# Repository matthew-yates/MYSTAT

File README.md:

## MYSTAT Potentiostat/Galvanostat

These are the design files for building and operating a compact open source potentiostat/galvanostat instrument.  The detailed technical specifications and instructions for operation can be found in the HardwareX article [MYSTAT: A compact potentiostat/galvanostat for general electrochemistry measurements](https://www.hardware-x.com/article/S2468-0672(20)30072-9/fulltext). The HardwareX article has a link to a static repository at [Zenodo](https://zenodo.org/records/4252476).  This github repository was created as a clone of the Zenodo repository, with the goal of facilitating the tracking of improvements to hardware design and development of control software.

The MYSTAT instrument design and control software is based on an earlier open source design published by [Thomas Dobbelaere](https://www.hardware-x.com/article/S2468-0672(17)30031-7/fulltext), who also created a [github repository](https://github.com/thomasdob/tdstatv3) for that instrument.

The voltage and current ranges of MYSTAT are significantly higher than the original design of Dobbelaere. The printed circuit board was completely redesigned. Only relatively minor changes were made to the Python control software and microcontroller firmware originally created by Dobbelaere.

This hardware and control software is fully open source, and changes/improvements are welcome.  An entirely open source tool chain was used for its development (KiCad, Python, and Linux).

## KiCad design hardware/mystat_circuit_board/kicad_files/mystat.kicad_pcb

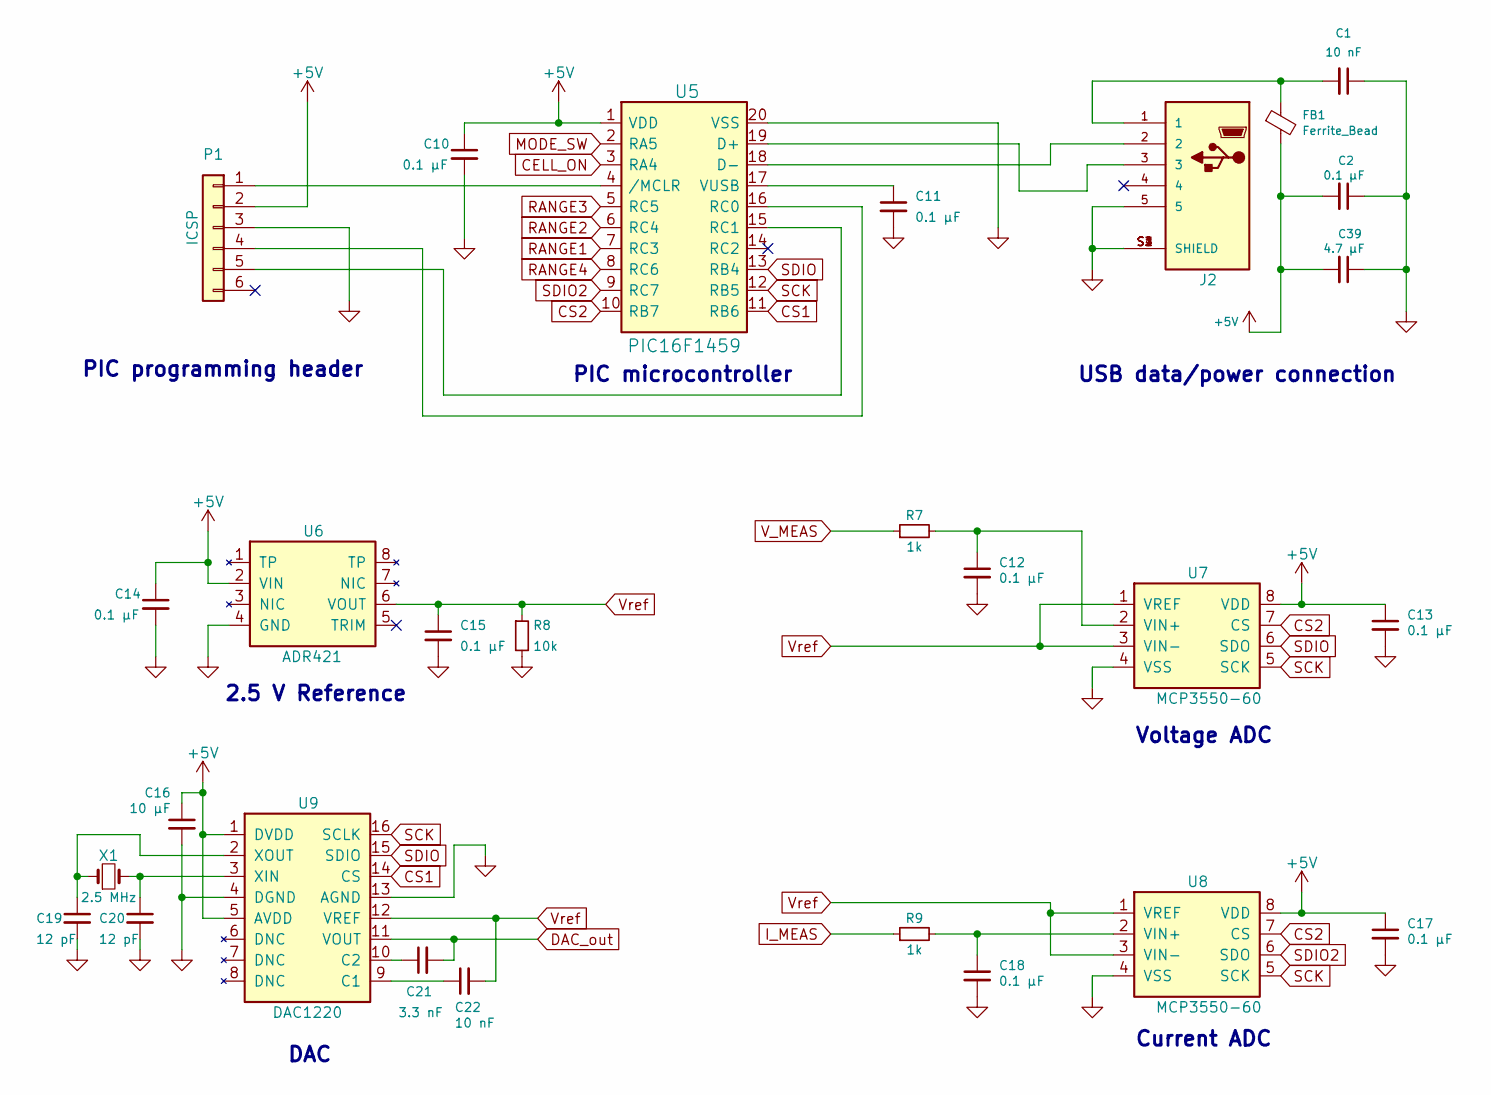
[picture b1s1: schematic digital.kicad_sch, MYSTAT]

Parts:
C1, C22: 10 nF; C_0805_2012Metric; Part Number C0805C103J5GACTU
C2, C10, C11, C12, C13, C14, C15, C17, C18: 0.1 µF; C_0805_2012Metric; Part Number 08055C104KAT2A
C16: 10 µF; C_1210_3225Metric; Part Number CL32B106KBJNNWE
C19, C20: 12 pF; C_0805_2012Metric; Part Number CC0805JRNPO9BN120
C21: 3.3 nF; C_0805_2012Metric; Part Number GRM2165C1H332JA01D
C39: 4.7 µF; C_0805_2012Metric; Part Number C2012X7R1V475K125AC
FB1: Ferrite_Bead; C_0805_2012Metric; Part Number ILBB0805ER320V
J2: 2173157-3; CONN_2173157-3; Part Number 2173157-3
P1: ICSP; PinHeader_1x06_P2.54mm_Vertical; Part Number PRPC006SAAN-RC
R7, R9: 1k; R_0805_2012Metric; Part Number RC0805FR-071KL
R8: 10k; R_0805_2012Metric; Part Number RC0805FR-0710KL
U5: PIC16F1459; SOIC-20W; Part Number PIC16F1459-I/SO
U6: ADR421; SOIC-8; Part Number ADR421ARZ
U7, U8: MCP3550-60; SOIC-8; Part Number MCP3550-60E/SN
U9: DAC1220; Part Number DAC1220E
X1: 2.5 MHz; Crystal_HC49-U_Vertical; Part Number ECS-25-S-1X

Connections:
+5V: C2.2, C10.1, C13.1, C14.1, C16.1, C17.1, C39.2, FB1.2, P1.2, U5.1 (VDD), U6.2 (VIN), U7.8 (VDD), U8.8 (VDD), U9.1 (DVDD), U9.5 (AVDD)
CELL_ON: U5.3 (RA4); also elsewhere on the board
CS1: U5.11 (RB6), U9.14 (CS)
CS2: U5.10 (RB7), U7.7 (CS), U8.7 (CS)
DAC_out: C21.2, U9.11 (VOUT); also elsewhere on the board
GND: C1.1, C2.1, C10.2, C11.2, C12.2, C13.2, C14.2, C15.2, C16.2, C17.2, C18.2, C19.2, C20.2, C39.1, J2.5, J2.S1 (SHIELD), J2.S2 (SHIELD), J2.S3 (SHIELD), J2.S4 (SHIELD), P1.3, R8.2, U5.20 (VSS), U6.4 (GND), U7.4 (VSS), U8.4 (VSS), U9.4 (DGND), U9.13 (AGND); also elsewhere on the board
I_MEAS: R9.1; also elsewhere on the board
MODE_SW: U5.2 (RA5); also elsewhere on the board
unnamed: C1.2, FB1.1, J2.1
unnamed: C11.1, U5.17 (VUSB)
unnamed: C12.1, R7.2, U7.2 (VIN+)
unnamed: C18.1, R9.2, U8.2 (VIN+)
unnamed: C19.1, U9.2 (XOUT), X1.1
unnamed: C20.1, U9.3 (XIN), X1.2
unnamed: C21.1, U9.10 (C2)
unnamed: C22.1, U9.9 (C1)
unnamed: J2.2, U5.18 (D-)
unnamed: J2.3, U5.19 (D+)
unnamed: P1.1, U5.4 (/MCLR)
unnamed: P1.4, U5.16 (RC0)
unnamed: P1.5, U5.15 (RC1)
RANGE1: U5.7 (RC3); also elsewhere on the board
RANGE2: U5.6 (RC4); also elsewhere on the board
RANGE3: U5.5 (RC5); also elsewhere on the board
RANGE4: U5.8 (RC6); also elsewhere on the board
SCK: U5.12 (RB5), U7.5 (SCK), U8.5 (SCK), U9.16 (SCLK)
SDIO: U5.13 (RB4), U7.6 (SDO), U9.15 (SDIO)
SDIO2: U5.9 (RC7), U8.6 (SDO)
V_MEAS: R7.1; also elsewhere on the board
Vref: C15.1, C22.2, R8.1, U6.6 (VOUT), U7.1 (VREF), U7.3 (VIN-), U8.1 (VREF), U8.3 (VIN-), U9.12 (VREF); also elsewhere on the board

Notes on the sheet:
PIC programming header
PIC microcontroller
DAC
2.5 V Reference
Voltage ADC
USB data/power connection
Current ADC

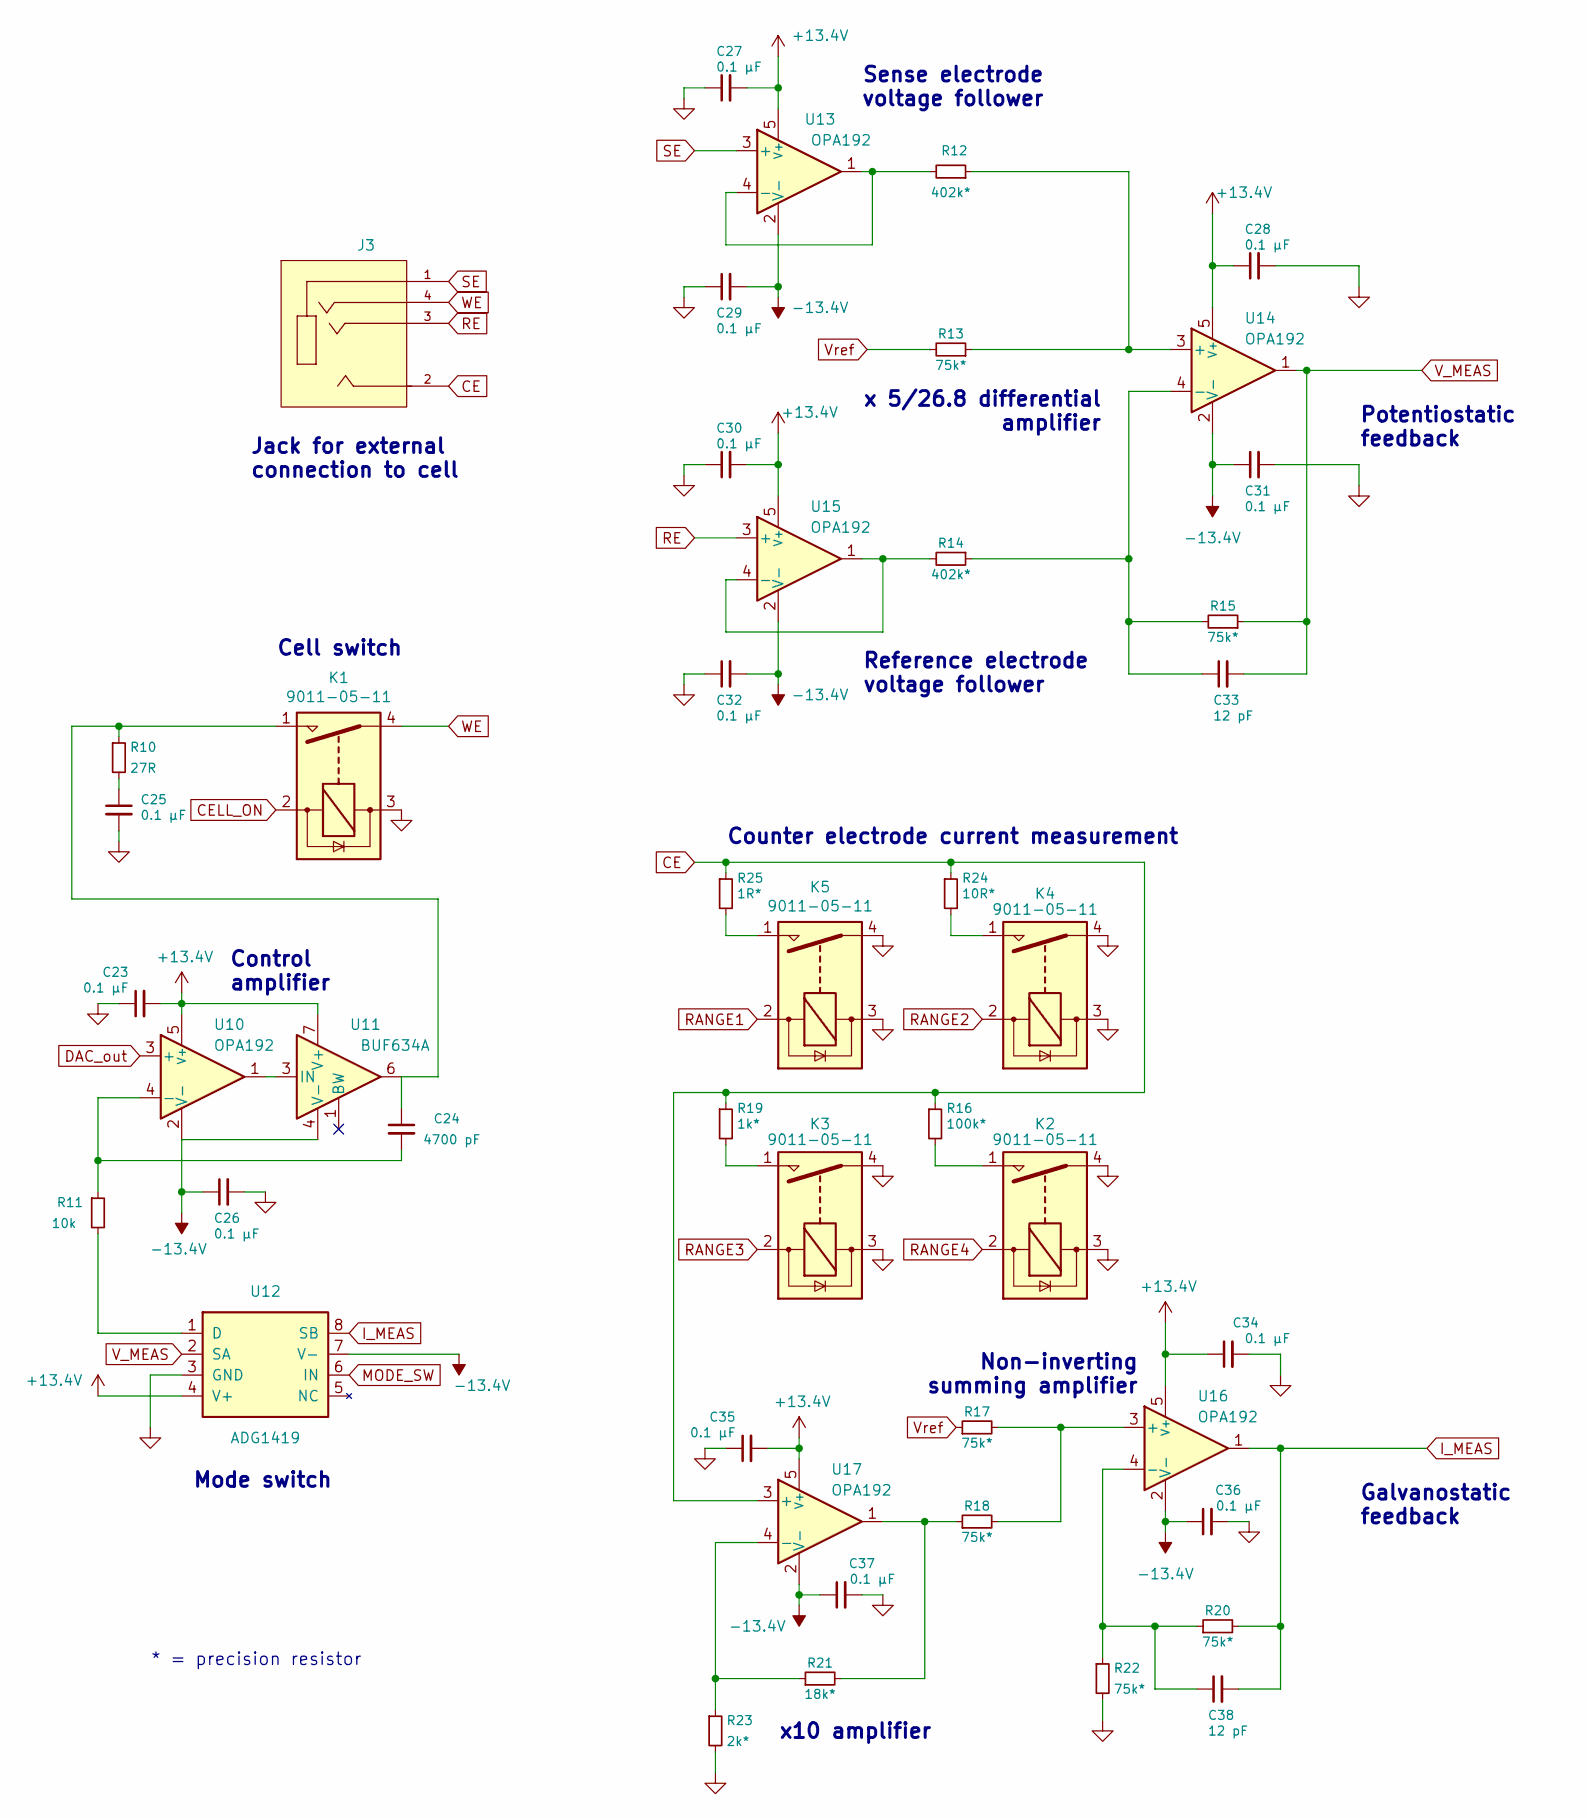
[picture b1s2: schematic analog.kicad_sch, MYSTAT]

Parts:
C23, C25, C26, C27, C28, C29, C30, C31, C32, C34, C35, C36, C37: 0.1 µF; C_0805_2012Metric; Part Number 08055C104KAT2A
C24: 4700 pF; C_0805_2012Metric; Part Number CC0805KRX7R9BB472
C33, C38: 12 pF; C_0805_2012Metric; Part Number CC0805JRNPO9BN120
J3: SJ1-42534-SMT; CUI_SJ1-42534-SMT; Part Number SJ1-42534-SMT-TR
K1, K2, K3, K4, K5: 9011-05-11; relay_9011-05-11; Part Number 9011-05-11
R10: 27R; R_0805_2012Metric; Part Number ERJ-6ENF27R0V
R11: 10k; R_0805_2012Metric; Part Number RC0805FR-0710KL
R12, R14: 402k*; R_0805_2012Metric; Part Number ERA-6AEB4023V
R13, R15, R17, R18, R20, R22: 75k*; R_0805_2012Metric; Part Number ERA-6AEB753V
R16: 100k*; R_0805_2012Metric; Part Number ERA-6AEB104V
R19: 1k*; R_0805_2012Metric; Part Number ERA-6AEB102V
R21: 18k*; R_0805_2012Metric; Part Number ERA-6AEB183V
R23: 2k*; R_0805_2012Metric; Part Number ERA-6AEB202V
R24: 10R*; R_0805_2012Metric; Part Number 2-1625868-7
R25: 1R*; R_0805_2012Metric; Part Number RL1220S-1R0-F
U10, U13, U14, U15, U16, U17: OPA192; Part Number OPA192IDBVR
U11: BUF634A; SOIC-8; Part Number BUF634AIDR
U12: ADG1419; MSOP-8_3x3mm_P0.65mm; Part Number ADG1419BRMZ-REEL7

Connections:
+13.4V: C23.2, C27.2, C28.1, C30.2, C34.1, C35.2, U10.5 (V+), U11.7 (V+), U12.4 (V+), U13.5 (V+), U14.5 (V+), U15.5 (V+), U16.5 (V+), U17.5 (V+); also elsewhere on the board
-13.4V: C26.1, C29.2, C31.1, C32.2, C36.1, C37.1, U10.2 (V-), U11.4 (V-), U12.7 (V-), U13.2 (V-), U14.2 (V-), U15.2 (V-), U16.2 (V-), U17.2 (V-); also elsewhere on the board
CE: J3.2, R16.1, R19.1, R24.1, R25.1, U17.3 (+)
CELL_ON: K1.2; also elsewhere on the board
DAC_out: U10.3 (+); also elsewhere on the board
GND: C23.1, C25.2, C26.2, C27.1, C28.2, C29.1, C30.1, C31.2, C32.1, C34.2, C35.1, C36.2, C37.2, K1.3, K2.3, K2.4, K3.3, K3.4, K4.3, K4.4, K5.3, K5.4, R22.2, R23.2, U12.3 (GND); also elsewhere on the board
I_MEAS: C38.2, R20.2, U12.8 (SB), U16.1; also elsewhere on the board
MODE_SW: U12.6 (IN); also elsewhere on the board
unnamed: C24.1, K1.1, R10.1, U11.6
unnamed: C24.2, R11.1, U10.4 (-)
unnamed: C25.1, R10.2
unnamed: C33.1, R14.1, R15.2, U14.4 (-)
unnamed: C38.1, R20.1, R22.1, U16.4 (-)
unnamed: K2.1, R16.2
unnamed: K3.1, R19.2
unnamed: K4.1, R24.2
unnamed: K5.1, R25.2
unnamed: R11.2, U12.1 (D)
unnamed: R12.1, R13.1, U14.3 (+)
unnamed: R12.2, U13.1, U13.4 (-)
unnamed: R14.2, U15.1, U15.4 (-)
unnamed: R17.2, R18.2, U16.3 (+)
unnamed: R18.1, R21.2, U17.1
unnamed: R21.1, R23.1, U17.4 (-)
unnamed: U10.1, U11.3 (IN)
RANGE1: K5.2; also elsewhere on the board
RANGE2: K4.2; also elsewhere on the board
RANGE3: K3.2; also elsewhere on the board
RANGE4: K2.2; also elsewhere on the board
RE: J3.3, U15.3 (+)
SE: J3.1, U13.3 (+)
V_MEAS: C33.2, R15.1, U12.2 (SA), U14.1; also elsewhere on the board
Vref: R13.2, R17.1; also elsewhere on the board
WE: J3.4, K1.4

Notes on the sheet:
Sense electrode voltage follower
Mode switch
x10 amplifier
Galvanostatic feedback
Non-inverting summing amplifier
* = precision resistor
Counter electrode current measurement
x 5/26.8 differential amplifier
Reference electrode voltage follower
Control amplifier
Cell switch
Potentiostatic feedback
Jack for external connection to cell

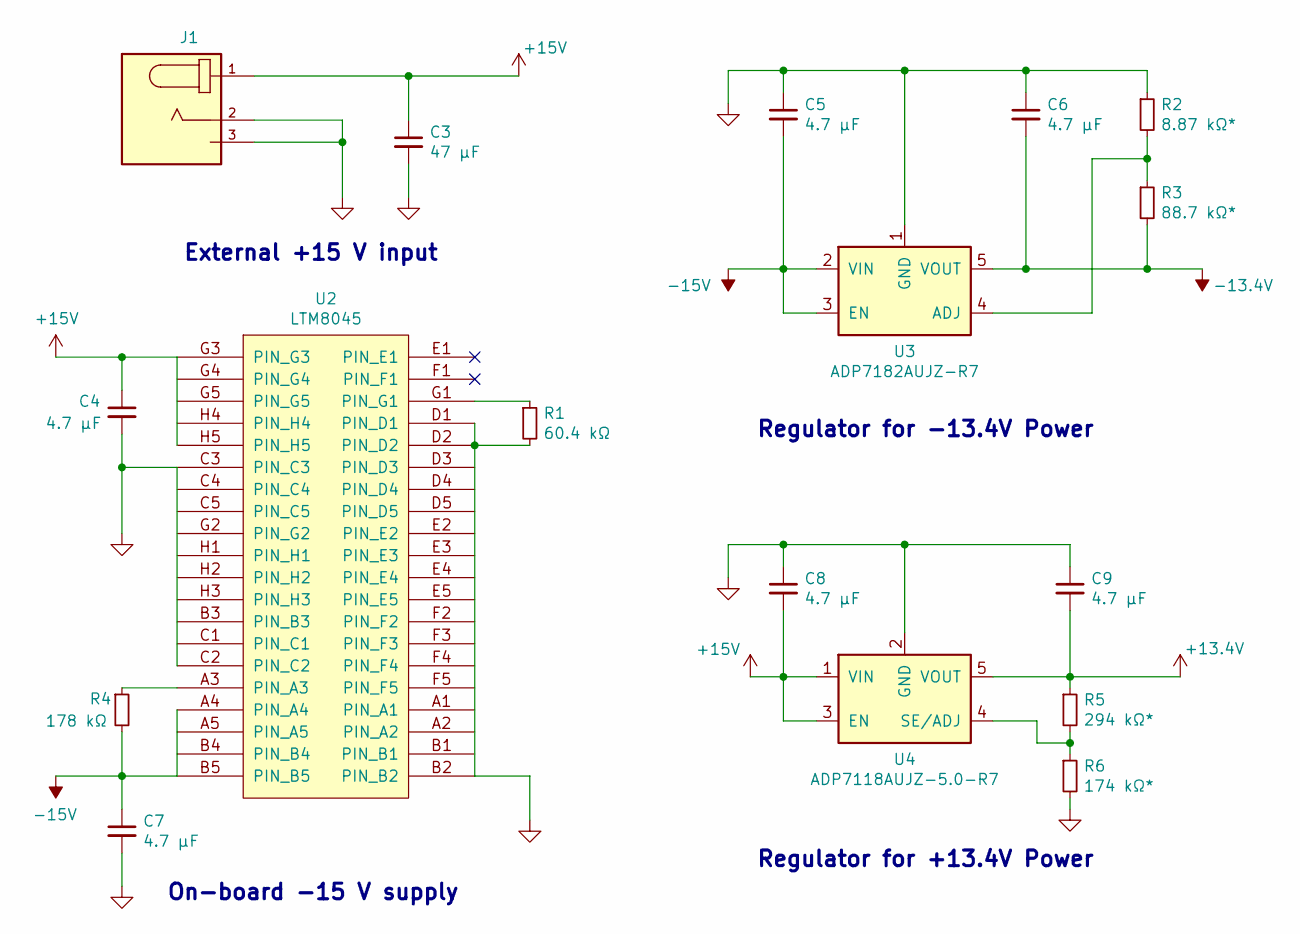
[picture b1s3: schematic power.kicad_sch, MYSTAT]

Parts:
C3: 47 μF; EEE-FT1V470AR; Part Number EEE-FT1V470AR
C4, C7: 4.7 μF; C_1206_3216Metric; Part Number CL31B475KBHNNNE
C5, C6, C8, C9: 4.7 µF; C_0805_2012Metric; Part Number C2012X7R1V475K125AC
J1: PJ-063AH; CUI_PJ-063AH; Part Number PJ-063AH
R1: 60.4 kΩ; R_0805_2012Metric; Part Number ERJ-6ENF6042V
R2: 8.87 kΩ*; R_0805_2012Metric; Part Number ERA-6AEB8871V
R3: 88.7 kΩ*; R_0805_2012Metric; Part Number ERJ-PB6B8872V
R4: 178 kΩ; R_0805_2012Metric; Part Number ERJ-6ENF1783V
R5: 294 kΩ*; R_0805_2012Metric; Part Number ERJ-PB6B2943V
R6: 174 kΩ*; R_0805_2012Metric; Part Number ERJ-PB6B1743V
U2: LTM8045; MODULE; Part Number LTM8045IY
U3: ADP7182AUJZ-R7; TSOT-23-5; Part Number ADP7182AUJZ-R7
U4: ADP7118AUJZ-5.0-R7; TSOT-23-5; Part Number ADP7118AUJZ-5.0-R7

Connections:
+13.4V: C9.2, R5.1, U4.5 (VOUT); also elsewhere on the board
+15V: C3.1, C4.1, C8.2, J1.1, U2.G3 (PIN_G3), U2.G4 (PIN_G4), U2.G5 (PIN_G5), U2.H4 (PIN_H4), U2.H5 (PIN_H5), U4.1 (VIN), U4.3 (EN)
-13.4V: C6.2, R3.2, U3.5 (VOUT); also elsewhere on the board
-15V: C5.2, C7.1, R4.2, U2.A4 (PIN_A4), U2.A5 (PIN_A5), U2.B4 (PIN_B4), U2.B5 (PIN_B5), U3.2 (VIN), U3.3 (EN)
GND: C3.2, C4.2, C5.1, C6.1, C7.2, C8.1, C9.1, J1.2, J1.3 (SHIELD), R1.2, R2.1, R6.2, U2.A1 (PIN_A1), U2.A2 (PIN_A2), U2.B1 (PIN_B1), U2.B2 (PIN_B2), U2.B3 (PIN_B3), U2.C1 (PIN_C1), U2.C2 (PIN_C2), U2.C3 (PIN_C3), U2.C4 (PIN_C4), U2.C5 (PIN_C5), U2.D1 (PIN_D1), U2.D2 (PIN_D2), U2.D3 (PIN_D3), U2.D4 (PIN_D4), U2.D5 (PIN_D5), U2.E2 (PIN_E2), U2.E3 (PIN_E3), U2.E4 (PIN_E4), U2.E5 (PIN_E5), U2.F2 (PIN_F2), U2.F3 (PIN_F3), U2.F4 (PIN_F4), U2.F5 (PIN_F5), U2.G2 (PIN_G2), U2.H1 (PIN_H1), U2.H2 (PIN_H2), U2.H3 (PIN_H3), U3.1 (GND), U4.2 (GND); also elsewhere on the board
unnamed: R1.1, U2.G1 (PIN_G1)
unnamed: R2.2, R3.1, U3.4 (ADJ)
unnamed: R4.1, U2.A3 (PIN_A3)
unnamed: R5.2, R6.1, U4.4 (SE/ADJ)

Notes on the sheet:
Regulator for -13.4V Power
Regulator for +13.4V Power
On-board -15 V supply
External +15 V input

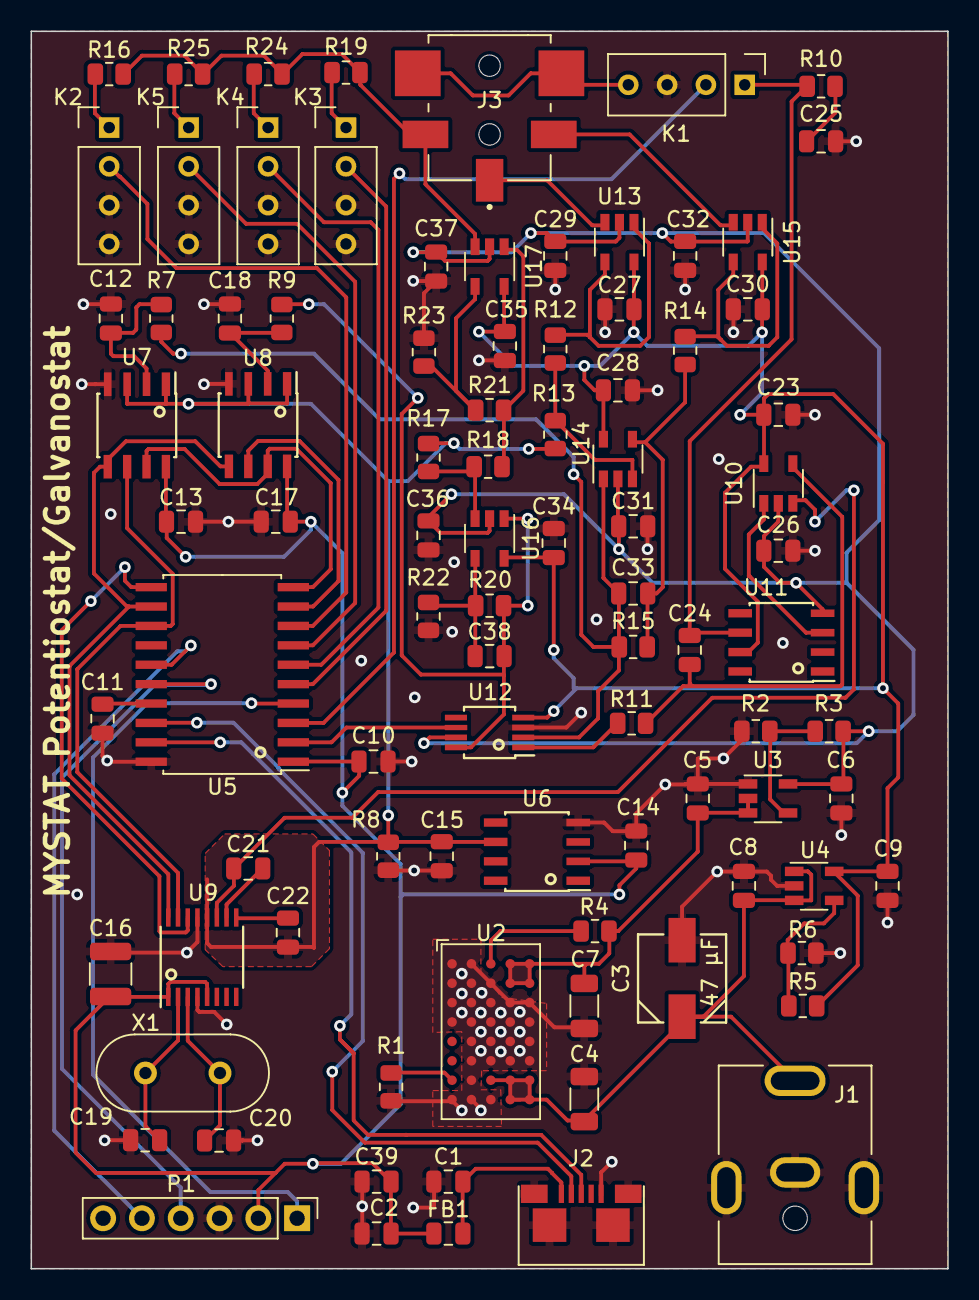
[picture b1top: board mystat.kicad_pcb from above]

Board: 4 copper layers, 60.0 x 81.0 mm, 91 parts (0 on the bottom side), 59 nets.

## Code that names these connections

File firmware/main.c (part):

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
#define _XTAL_FREQ 48000000     // 48 MHz CPU clock frequency

#define MODE_SW_PIN LATAbits.LATA5
#define MODE_SW_TRIS TRISAbits.TRISA5
#define CELL_ON_PIN LATAbits.LATA4
#define CELL_ON_TRIS TRISAbits.TRISA4
#define CELL_ON  1
#define CELL_OFF 0
#define POTENTIOSTATIC  0
#define GALVANOSTATIC  1
#define INPUT  1
#define OUTPUT 0
#define RANGE1_PIN LATCbits.LATC3
#define RANGE1_TRIS TRISCbits.TRISC3
#define RANGE2_PIN LATCbits.LATC4
#define RANGE2_TRIS TRISCbits.TRISC4
#define RANGE3_PIN LATCbits.LATC5
#define RANGE3_TRIS TRISCbits.TRISC5
#define RANGE4_PIN LATCbits.LATC6
#define RANGE4_TRIS TRISCbits.TRISC6

static const uint8_t* received_data;
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	ANSELC = 0x00; // digital I/O on PORTC
	APFCON = 0x00; // no funny alternate pins
	MODE_SW_TRIS = OUTPUT;
	MODE_SW_PIN = POTENTIOSTATIC; // initialize mode to potentiostatic
	CELL_ON_TRIS = OUTPUT;
	CELL_ON_PIN = CELL_OFF; // initialize cell to off position
	RANGE1_TRIS = OUTPUT;
	RANGE2_TRIS = OUTPUT;
	RANGE3_TRIS = OUTPUT;
	RANGE4_TRIS = OUTPUT;
	RANGE1_PIN = 1; // initialize range to range 1
	RANGE2_PIN = 0;
	RANGE3_PIN = 0;
	RANGE4_PIN = 0;
	InitializeSPI();
	__delay_ms(25); // power-up delay - necessary for DAC1220
	DAC1220_Reset();
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
void command_cell_on()
{
	CELL_ON_PIN = CELL_ON;
	send_OK();
}

void command_cell_off()
{
	CELL_ON_PIN = CELL_OFF;
	send_OK();
}

void command_mode_potentiostatic()
{
	MODE_SW_PIN = POTENTIOSTATIC;
	send_OK();
}

void command_mode_galvanostatic()
{
	MODE_SW_PIN = GALVANOSTATIC;
	send_OK();
}

void command_range1()
{
    RANGE1_PIN = 1;
    __delay_ms(10); // make the new relay setting before breaking the old one
    RANGE2_PIN = 0;
    RANGE3_PIN = 0;
    RANGE4_PIN = 0;
	send_OK();
}

void command_range2()
{
    RANGE2_PIN = 1;
    __delay_ms(10); // make the new relay setting before breaking the old one
    RANGE1_PIN = 0;
    RANGE3_PIN = 0;
    RANGE4_PIN = 0;
	send_OK();
}

void command_range3()
{
    RANGE3_PIN = 1;
    __delay_ms(10); // make the new relay setting before breaking the old one
    RANGE1_PIN = 0;
    RANGE2_PIN = 0;
    RANGE4_PIN = 0;
	send_OK();
}

void command_range4()
{
    RANGE4_PIN = 1;
    __delay_ms(10); // make the new relay setting before breaking the old one
    RANGE1_PIN = 0;
    RANGE2_PIN = 0;
    RANGE3_PIN = 0;
	send_OK();
}

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
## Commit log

2024-04-24 Adding all files & folders under the project
2024-04-24 Create LICENSE
2024-04-24 Update LICENSE
2024-05-04 Delete hardware/backpanel/kicad_files/backpanel.sch
    updating to new KiCad file formats
2024-05-04 Add files via upload
    update to KiCad version 6.0 in Debian 12.5
2024-05-04 Delete hardware/backpanel/kicad_files/backpanel.pro
    updating to new file formats
2024-05-04 Delete hardware/backpanel/kicad_files/backpanel.kicad_pcb
    updating to new KiCad file formats
2024-05-04 Add files via upload
    KiCad version 6.0 from Debian 12.5
2024-05-04 Add files via upload
    KiCad 6.0 from Debian 12.5
2024-05-04 Add files via upload
    created with KiCad 6.0 from Debian 12.5
2024-05-04 Delete hardware/backpanel/gerber_files/backpanel-B.Adhes.gba
    replaced with new KiCad version
2024-05-04 Delete hardware/backpanel/gerber_files/backpanel-B.CrtYd.gbr
    replaced with new KiCad version
2024-05-04 Delete hardware/backpanel/gerber_files/backpanel-B.Cu.gbl
    replaced with new KiCad version
2024-05-04 Delete hardware/backpanel/gerber_files/backpanel-B.Fab.gbr
    replaced with new KiCad version
2024-05-04 Delete hardware/backpanel/gerber_files/backpanel-B.Mask.gbs
    replaced with new KiCad version
2024-05-04 Delete hardware/backpanel/gerber_files/backpanel-B.Paste.gbp
    replaced with new KiCad version
2024-05-04 Delete hardware/backpanel/gerber_files/backpanel-B.SilkS.gbo
    replaced with new KiCad version
2024-05-04 Delete hardware/backpanel/gerber_files/backpanel-Edge.Cuts.gm1
    replaced with new KiCad version
2024-05-04 Delete hardware/backpanel/gerber_files/backpanel-F.Adhes.gta
    replaced with new KiCad version
2024-05-04 Delete hardware/backpanel/gerber_files/backpanel-F.CrtYd.gbr
    replaced with new KiCad version
2024-05-04 Delete hardware/backpanel/gerber_files/backpanel-F.Cu.gtl
    replaced with new KiCad version
2024-05-04 Delete hardware/backpanel/gerber_files/backpanel-F.Fab.gbr
    replaced with new KiCad version
2024-05-04 Delete hardware/backpanel/gerber_files/backpanel-F.Mask.gts
    replaced with new KiCad version
2024-05-04 Delete hardware/backpanel/gerber_files/backpanel-F.Paste.gtp
    replaced with new KiCad version
2024-05-04 Delete hardware/backpanel/gerber_files/backpanel-F.SilkS.gto
    replaced with new KiCad version
2024-05-04 Add files via upload
    Minor changes allowing KiCad design rules check to complete without error
2024-05-04 Add files via upload
    minor changes to allow KiCad design rules check to complete without errors or warnings
2024-05-04 Delete hardware/backpanel/backpanel_image.png
    replaced with version created in KiCad 6.0
2024-05-04 Add files via upload
    PCB image from KiCad 6.0 3D viewer
2024-05-04 Delete hardware/frontpanel/kicad_files/frontpanel.kicad_pcb
    replaced with file from KiCad 6.0 from Debian 12.5
2024-05-04 Delete hardware/frontpanel/kicad_files/frontpanel.pro
    replaced with file from KiCad 6.0 from Debian 12.5
2024-05-04 Delete hardware/frontpanel/kicad_files/frontpanel.sch
    replaced with file from KiCad 6.0 from Debian 12.5
2024-05-04 Create d
2024-05-04 Add files via upload
    update to KiCad 6.0 from Debian 12.5
2024-05-04 Delete hardware/frontpanel/frontpanel_image.png
    replaced with new version
2024-05-04 Add files via upload
    created with KiCad 6.0 3D viewer
2024-05-04 Delete hardware/frontpanel/gerber_files/frontpanel-B.Adhes.gba
    replaced with files created in KiCad 6.0 from Debian 12.5
2024-05-04 Delete hardware/frontpanel/gerber_files/frontpanel-B.CrtYd.gbr
    replaced with files created in KiCad 6.0 from Debian 12.5
2024-05-04 Delete hardware/frontpanel/gerber_files/frontpanel-B.Cu.gbl
    replaced with files created in KiCad 6.0 from Debian 12.5
2024-05-04 Delete hardware/frontpanel/gerber_files/frontpanel-B.Fab.gbr
    replaced with files created in KiCad 6.0 from Debian 12.5
2024-05-04 Delete hardware/frontpanel/gerber_files/frontpanel-B.Mask.gbs
    replaced with files created in KiCad 6.0 from Debian 12.5
2024-05-04 Delete hardware/frontpanel/gerber_files/frontpanel-B.Paste.gbp
    replaced with files created in KiCad 6.0 from Debian 12.5
2024-05-04 Delete hardware/frontpanel/gerber_files/frontpanel-B.SilkS.gbo
    replaced with files created in KiCad 6.0 from Debian 12.5
2024-05-04 Delete hardware/frontpanel/gerber_files/frontpanel-Edge.Cuts.gm1
    replaced with files created in KiCad 6.0 from Debian 12.5
2024-05-04 Delete hardware/frontpanel/gerber_files/frontpanel-F.Adhes.gta
    replaced with files created in KiCad 6.0 from Debian 12.5
2024-05-04 Delete hardware/frontpanel/gerber_files/frontpanel-F.CrtYd.gbr
    replaced with files created in KiCad 6.0 from Debian 12.5
2024-05-04 Delete hardware/frontpanel/gerber_files/frontpanel-F.Cu.gtl
    replaced with files created in KiCad 6.0 from Debian 12.5
2024-05-04 Delete hardware/frontpanel/gerber_files/frontpanel-F.Fab.gbr
    replaced with files created in KiCad 6.0 from Debian 12.5
2024-05-04 Delete hardware/frontpanel/gerber_files/frontpanel-F.Mask.gts
    replaced with files created in KiCad 6.0 from Debian 12.5
2024-05-04 Delete hardware/frontpanel/gerber_files/frontpanel-F.Paste.gtp
    replaced with files created in KiCad 6.0 from Debian 12.5
2024-05-04 Delete hardware/frontpanel/gerber_files/frontpanel-F.SilkS.gto
    replaced with files created in KiCad 6.0 from Debian 12.5
2024-05-04 Add files via upload
    created with KiCad 6.0 on Debian 12.5
2024-05-05 Delete hardware/mystat_circuit_board/circuit_board_image.png
    replaced with new version from KiCad 6.0
2024-05-05 Add files via upload
    from KiCad 6.0 3D viewer
2024-05-05 Add files via upload
    new schematics from KiCad 6.0
2024-05-05 Delete hardware/mystat_circuit_board/kicad_files/analog.sch
    replaced with new version
2024-05-05 Delete hardware/mystat_circuit_board/kicad_files/digital.sch
    replaced with new version
2024-05-05 Delete hardware/mystat_circuit_board/kicad_files/mystat.sch
    replaced with new version
2024-05-05 Delete hardware/mystat_circuit_board/kicad_files/power.sch
    replaced with new version
2024-05-05 Add files via upload
    new version from KiCad 6.0
2024-05-05 Delete hardware/mystat_circuit_board/kicad_files/mylib.lib
    replaced with new version
2024-05-05 Delete hardware/mystat_circuit_board/kicad_files/mystat.pro
    replaced with new version
2024-05-05 Add files via upload
    from KiCad 6.0
2024-05-05 Add files via upload
    minor changes in KiCad 6.0 so that design rules checkers completes without warnings
2024-05-05 Delete hardware/mystat_circuit_board/gerber_files/mystat-B_Adhes.gba
    replaced with new version
2024-05-05 Delete hardware/mystat_circuit_board/gerber_files/mystat-B_CrtYd.gbr
    replaced with new version
2024-05-05 Delete hardware/mystat_circuit_board/gerber_files/mystat-B_SilkS.gbo
    replaced with new version
2024-05-05 Delete hardware/mystat_circuit_board/gerber_files/mystat-F_Adhes.gta
    replaced with new version
2024-05-05 Delete hardware/mystat_circuit_board/gerber_files/mystat-F_CrtYd.gbr
    replaced with new version
2024-05-05 Delete hardware/mystat_circuit_board/gerber_files/mystat-F_SilkS.gto
    replaced with new version
2024-05-05 Delete hardware/mystat_circuit_board/gerber_files/mystat.drl
    replaced with new version
2024-05-07 Add files via upload
    Update to KiCad 7.0 from Debian bookworm backports
2024-05-07 Add files via upload
    Updated files produced by KiCad 7.0
2024-05-07 Add files via upload
    Updated files to KiCad 7.0 from Debian bookworm backports
2024-05-07 Add files via upload
    Updated to files produced from KiCad 7.0
2024-05-07 Update README.md
    added instructions to workaround the pyqtgraph incompatibility,
2024-05-07 Add files via upload
    minor footprint edits to pass KiCad 7.0 design rules checks
2024-05-07 Add files via upload
    Minor re-routing tracks on PCB to pass KiCad 7.0 design rules checks
2024-05-07 Add files via upload
    Updated version to pass KiCad 7.0 design rules checks
2024-05-07 Add files via upload
    Updated labels on schematics
2024-05-07 Add files via upload
    Minor routing change and edit back silkscreen.

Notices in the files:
parts and their libraries:
Copyright 2016 Accelerated Designs. All rights reserved.
